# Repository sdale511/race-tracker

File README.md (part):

# Race Tracker — Boat Agent + Base Station

Reports GPS position from a boat (Pi Zero 2 W + simpleRTK2B LR) to a shore/
committee base station over a long-range telemetry radio (>2 mi), with
logging to microSD as a durable backup.

## Architecture

```
[simpleRTK2B LR]--UART-->[Pi Zero 2 W]--UART-->[Telemetry radio]==RF==>[Telemetry radio]--UART-->[Base station]--> race software
                              |
                              v
                    microSD (CSV, same fixes sent over radio)
```

For the complete rover → base → RegattaUp data flow - wire formats, Redis
keys, webhook payloads, RegattaUp's own entity fields - see
[`docs/telemetry-pipeline.html`](docs/telemetry-pipeline.html) (open in a
browser).

| Component | Notes |
|---|---|
| GPS | ZED-F9P, `UBX-NAV-PVT` binary messages (position, speed, heading, fix type, RTK carrier solution, satellite count) - no NMEA needed |
| Radio | Digi XBee 900 MHz in transparent serial mode (any transparent-serial radio works, e.g. RFD900x/SiK). A compact 26-byte binary frame (`src/protocol.js`) minimizes airtime - batched 8 at a time by default (delta-coded, 83 bytes), see `TX_BATCH_SIZE` below |
| SD log | Logged exactly when a fix clears the `TX_DISTANCE_M`/`TX_INTERVAL_S` gate - same gate as the radio send, so the SD record mirrors what actually transmitted rather than a separate full-rate trace |

**How the gate measures.** A fix clears the gate when the boat has moved `TX_DISTANCE_M` (default 1 m) from the last fix that *cleared* it, or `TX_INTERVAL_S` (default 60 s) has passed since then - the last fix that cleared the gate, not the last one actually sent (`distanceGate.js`). In slot mode a fix waits up to a cycle for its slot; measured from the last fix *sent*, the gate stayed open for that whole wait, so a boat creeping at 1.3 kn sent clusters of eight fixes a millimetre apart, then nothing for two seconds, and a heartbeat that fell due sent eight copies of one position. Now consecutive fixes are at least `TX_DISTANCE_M` apart and a heartbeat adds one fix. A boat faster than about 19 kn at 10 Hz moves more than a metre per fix, so it still sends every fix. A send that fails (radio not connected yet) hands the reference back to the last fix that really went out, so the boat keeps retrying.

## Wiring notes

Default config uses the Pi's own dedicated hardware UART (`/dev/ttyAMA0`,
GPIO 14/15 - avoid the mini-UART, its clock is tied to the core clock and
can glitch), leaving the one USB/OTG port free for the telemetry radio
alone.

```
sudo raspi-config   # Interface Options -> Serial Port
                     # "login shell over serial" = No
                     # "serial port hardware enabled" = Yes
```

- Prefer the simpleRTK2B's own USB port (`/dev/ttyACM0`) instead? Set
  `GPS_PORT=/dev/ttyACM0` (and matching `GPS_BAUD`) - simpler wiring, but
  needs a USB hub since the radio then needs its own USB-to-serial adapter.
- Any Pi with onboard Bluetooth (Zero 2 W, 3A+/3B+, 4, ...) puts GPIO14/15
  on the glitch-prone mini-UART (`ttyS0`) by default, since Bluetooth
  occupies the real UART. Fix:
  ```
  # /boot/firmware/config.txt (Bookworm+) or /boot/config.txt (older)
  dtoverlay=disable-bt
  ```
  then disable `hciuart`/`bluetooth` services and reboot.
- Which physical UART (UART1 vs UART2) your wiring reaches depends on the
  board - ArduSimple's simpleRTK2B routes UART2 to the XBee socket (used
  for RTCM correction radios, unrelated to this app), so a general
  breakout pin is more likely UART1 - verify, don't assume (see below).

### Radio sleep wiring (XBee SLEEP_RQ)

Optional - only needed for rover radio sleep mode (see "Radio sleep mode"
below). One extra wire from a Pi GPIO to the XBee's SLEEP_RQ pin, next to
the radio's UART wiring above:

| From | To | Notes |
|---|---|---|
| Pi **GPIO17** (header pin 11, 3.3 V) | XBee **pin 9** (SLEEP_RQ / DTR) | High = radio asleep, low = awake |
| Pi GND (header pin 9, right next to pin 11) | XBee GND | Shared ground, usually already there via the UART wiring |
| 10 kohm resistor | XBee pin 9 to GND | Pull-down, so the radio stays awake while the Pi is off or still booting |

- **Why GPIO17:** GPIO9-27 are pulled *down* at boot, whereas GPIO0-8 are
  pulled *up* and would put the radio to sleep during every Pi boot. GPIO17
  also isn't claimed by anything this app uses or by a default overlay (UART
  GPIO14/15, I2C GPIO2/3, SPI GPIO7-11, 1-wire GPIO4, PWM/PCM GPIO12/13/18/19),
  and sits on header pin 11 with GND on pin 9 beside it, so one short
  cable can carry the UART (pins 8/10) and this wire. Any other free GPIO
  from 9-27 works; set `RADIO_SLEEP_GPIO` to its BCM number.
- **XBee setting:** the radio must be in pin-sleep mode - `ATSM1`, then `ATWR`
  (for example from XCTU). `xbee_configure_at.py` does not set this. Do it only
  once the wire and pull-down are in place, because in `SM=1` a pin driven
  high puts the radio to sleep and it cannot be reached over the UART until
  the pin goes low again.
- **If the radio is on a USB-serial bridge** whose DTR line is also wired to
  XBee pin 9 (needed only for serial firmware updates), use a jumper or
  solder bridge so just one of the two drives the pin - never both.
- Optional: XBee ON_SLEEP (pin 13) to a spare Pi GPIO input, or an LED, to
  see the radio's actual sleep state. The app doesn't read it.
- `RADIO_SLEEP_GPIO=17` tells the rover app which pin to drive. Unset (the
  default), a real rover ignores sleep commands. It uses Raspberry Pi OS's
  `pinctrl` command to drive the pin.

### GPS backup battery (V_BCKP)

Not a wire - a factory option on the ArduSimple board. It keeps the GPS's
satellite data alive so the rover restarts hot instead of cold. Whether your board
needs it is something to check, not assume: see "Checking and fitting the GPS
backup battery" under "Radio sleep mode".

## GPS configuration (one-time, from a computer)

The rovers never configure the GPS module or the radio - the Pi only reads fixes. Set the ZED-F9P up from a computer
over the board's own USB port, with `ubx_config_set.py` (or u-center):

```
pip install pyserial
python3 ubx_config_set.py --port <the board's USB port> --role rover-pi --dry-run   # shows what it would change
python3 ubx_config_set.py --port <the board's USB port> --role rover-pi
```

`rover-pi` is the Pi rover's profile and keeps UART2 on, so the XBee in the board's socket feeds the receiver directly.
Plain `rover` is the ESP32 rover's (`firmware/esp32-rover`), which switches UART2 **off** - don't use it on a Pi boat,
whose corrections would then stop reaching the receiver.

The rover profile turns `UBX-NAV-PVT` on (without it this app sees nothing), sets 10 Hz, disables TMODE3, turns
`UBX-RXM-RTCM` on, sets UART2's baud to match the XBee in the board's socket, and sets UART1 (the port the Pi reads) to
115200 with UBX output on. It writes to RAM, BBR and flash, so it
survives a power cycle, and reads every value back. Each UART is configured independently - the UART the Pi's wires reach
may still be at factory defaults (NMEA on, UBX off) even after another port was configured. The profile sets
`UBX-NAV-PVT` on UART1; if the Pi's wires reach UART2, check with the verification step below. The XBee is configured
separately with `xbee_configure_at.py`. Don't install `gpsd` on a rover - it grabs the serial port.

To see what a port is outputting before you configure anything, try the common bauds (9600, 19200, 38400, 57600,
115200) until you see clean `$GNGGA`/`$GNRMC`/... text:

```
stty -F /dev/ttyAMA0 <baud> raw -echo
cat /dev/ttyAMA0        # Ctrl-C to stop
```

`sudo ./setup-pi.sh uart` on the Pi only frees the UART (serial console off, Bluetooth off, `dialout` group); it does not touch
the GPS module.

### Checking the antenna gets both bands

Dual-band RTK needs L2 as well as L1, and an antenna that only passes L1 still gives a normal-looking fix. While a rover's
dashboard is open, its **GPS signals** card asks the receiver for `UBX-NAV-SIG` every few seconds and shows satellites and
average C/N0 per band and per constellation, with a verdict: L1 + L2, L2 weak, L1 only, or too few satellites to judge.
"L2" includes Galileo E5b and BeiDou B2I, and a gap of a few dB under L1 is normal. The weak thresholds in
`src/gnssSignals.js` are rules of thumb. The card also shows whether the telemetry radio hurts reception: compare it with
the radio transmitting and silent. It needs the Pi TX line wired to the receiver RX, and it doesn't ask while the GPS
sleeps, because any byte would wake it. Nothing on the receiver is reconfigured.

### Verifying the connection

```
stty -F /dev/ttyAMA0 115200 raw -echo
cat /dev/ttyAMA0        # expect quiet gaps + a short binary burst ~1/sec
```
Then confirm this app itself decodes it (the check that actually matters):
```
GPS_PORT=/dev/ttyAMA0 GPS_BAUD=115200 npm run boat
```
Watch for `[gps]` lines with real `fixType`/`numSV` (see `GPS_LOG`; `npm run print-config` lists every
setting). Silence means `UBX-NAV-PVT` went to the wrong UART number
- undo (`CFG-MSGOUT-UBX_NAV_PVT_UARTx,0,7`) and try the other.

The simpleRTK2B LR's onboard radio (in the board's XBee socket) is a
**separate concern** - it carries RTCM3 correction data between RTK base
and this rover, not position telemetry. "LR" is ArduSimple's own kit name
("Long Range," about 10 km), not a Digi product name - confirmed off the
module's label, the chip is a **Digi XBee SX** (Model XBSX, FCC ID
`MCQ-XBSX`); the step-up "XLR" kit uses a Digi XBee PRO SX for longer
range.

### RTK base GPS: enabling RTCM3 output (one-time)

`TMODE3` (fixed/survey-in position, set from this app's `npm run
rtk`/`basertk` dashboard) and RTCM3 *output* are separate config groups -
setting a fixed position doesn't turn sending RTCM on. Some kits ship with
only `1005` enabled and no observation messages, which looks like "locked
and working" on the dashboard while the rover receives nothing usable.

Check/enable on the base's correction-radio UART (`UART2` on the
simpleRTK2B LR - its onboard XBee SX is wired internally to UART2, not
something you'd jumper yourself):

| Message | Content |
|---|---|
| `1005` | Station coordinates (depends on the fixed position) |
| `1074`/`1084`/`1094`/`1124` | MSM4 observations: GPS/GLONASS/Galileo/BeiDou |
| `1230` | GLONASS code-phase biases (needed alongside `1084`) |

Send **one** observation set, MSM4, not MSM4 and MSM7 together. MSM7 carries
the same observations at higher resolution and about 1.5x the bytes; sending
both is duplicate traffic (an audit found a board doing exactly that - the
factory MSM4 plus an MSM7 set added on top - roughly 2.5x the bytes the rover
needs). MSM4 is also the better fit for this fleet's radios: a whole epoch is
about 400 bytes, and individual messages stay near the 100-byte radio packet
limit (MSM7 messages go well past it and get split in two over the air, and
losing either half loses the message).

```
ubxtool -f <base GPS port> -s <baud> -P 27.11 -z CFG-MSGOUT-RTCM_3X_TYPE1005_UART2,1,7
ubxtool -f <base GPS port> -s <baud> -P 27.11 -z CFG-MSGOUT-RTCM_3X_TYPE1074_UART2,1,7
ubxtool -f <base GPS port> -s <baud> -P 27.11 -z CFG-MSGOUT-RTCM_3X_TYPE1084_UART2,1,7
ubxtool -f <base GPS port> -s <baud> -P 27.11 -z CFG-MSGOUT-RTCM_3X_TYPE1094_UART2,1,7
ubxtool -f <base GPS port> -s <baud> -P 27.11 -z CFG-MSGOUT-RTCM_3X_TYPE1124_UART2,1,7
ubxtool -f <base GPS port> -s <baud> -P 27.11 -z CFG-MSGOUT-RTCM_3X_TYPE1230_UART2,1,7
```
`ubx_config_set.py --role base` (below) does all of this on both UART1 and
UART2 and also switches the MSM7 messages off, which these commands alone don't.
Only enable constellations you're actually tracking. `,7` saves to flash
immediately (bare `,1` is RAM-only, for testing before committing).

For visibility into corrections arriving rover-side, enable `UBX-RXM-RTCM`
on the rover's own GPS UART and set `RTCM_LOG=1` (off by default; `GPS_LOG_RTCM` is the old name and still works):
```
ubxtool -f /dev/ttyAMA0 -s <baud> -P 27.11 -z CFG-MSGOUT-UBX_RXM_RTCM_UART1,1,7
```
Watch `[rtcm]` lines (`type=1074 station=0 used=used`) - `used=not used` on
its own is normal (unused constellations), `CRC-FAILED` means a correction
arrived corrupted. Message counts/CRC failures are always tracked
internally (`GET /api/stats`) regardless of this flag.

### RTK base GPS: enabling the survey-in status card (optional)

If the "Base GPS survey-in" card shows "no base GPS, or not polled yet"
even with `GPS_PORT` set and TMODE3 configured for survey-in,
`UBX-NAV-SVIN` likely isn't enabled as an output:
```
ubxtool -f /dev/ttyAMA0 -s 115200 -P 27.11 -z CFG-MSGOUT-UBX_NAV_SVIN_UART1,1,7
```
Configuring TMODE3 itself for survey-in (vs. just reading it) is a
separate one-time step, typically done via u-center at setup - see
u-blox's ZED-F9P integration manual for survey-in parameters.

### Checking everything at once (ubx_config_report.py)

`ubx_config_report.py` polls every setting the sections above depend on - fix rate, UART baud,
`UBX-NAV-PVT`/NMEA/`UBX-NAV-SVIN`/`UBX-RXM-RTCM` output, TMODE3 mode, RTCM3 output types - in one pass, instead of
polling each by hand or assuming a board's still configured the way it was last time. It talks the UBX binary protocol
directly over `pyserial` (no `gpsd`/`ubxtool` needed - same reasoning as `xbee_configure_at.py`'s own "why not a
library" comment) and is read-only:
```
pip install pyserial
python3 ubx_config_report.py --port /dev/ttyAMA0 --baud 115200
```
A board acting as a rover should show the RTK-base rows (TMODE3, RTCM3 output) at 0/off; a board acting as the RTK base
should show its own rows enabled and `CFG-TMODE-MODE` non-zero. `--comms` instead measures the bytes sent and received
on each port over a few seconds (`--comms-seconds`, default 5). Every key ID it polls is cross-checked against two
independent open-source references (SparkFun's u-blox GNSS library and pyubx2), not typed from memory - see its own
module comment.

`ubx_config_set.py` applies the fix, same no-`ubxtool`-needed approach:
```
python3 ubx_config_set.py --port /dev/ttyAMA0 --baud 115200 --role base
python3 ubx_config_set.py --port /dev/ttyAMA0 --baud 115200 --role rover-pi
```
`--role base` makes the base's RTCM output clean: `1005`, the MSM4 observations
(`1074`/`1084`/`1094`/`1124` - GPS/GLONASS/Galileo/BeiDou) and `1230` on, the
MSM7 messages (`1077`/`1087`/`1097`/`1127`) explicitly off, RTCM3 allowed as an
output protocol, and `UBX-NAV-SVIN` on - on the ports named by `--rtcm-ports`
(default `uart2,usb`: UART2 is the onboard correction radio, USB the host
connection), with every other port's RTCM switched off so nothing is sent where
nothing reads it. Add `uart1` only if something reads the board on the Pi header
UART. `--constellations` (default all four) leaves constellations out to save
bytes - a left-out one has its MSM4 message off, and `1230` goes with GLONASS.
`--rtcm-interval N` (default 2) sends every enabled message every N seconds instead of every
second (it sets the messages' output rate in measurement epochs, and the base profile also sets the receiver's
measurement rate to 1 Hz so an epoch is a second - at the rover profile's 10 Hz, "2 epochs" would be 0.2 s, about eight
times the intended correction airtime, which is what happens if the rover profile is ever applied to a base receiver):
`--rtcm-interval 2` halves the correction airtime, at the cost of rovers working from corrections up
to 2 s old and a lost message costing 2 s. Check that RTK still holds at speed before relying on it.
`--station-interval N` (default 10) sends the 1005 station-position message every N seconds instead of with every burst
(never more often than `--rtcm-interval`). The base's position is fixed, so a rover only needs to hear it now and then; it
is what a rover needs before it can start an RTK fix, so a boat that powers up waits up to N seconds for its first one.
Sending it less often also removes a small message that would otherwise arrive a second away from the observations.

Run it with `--dry-run` first to see exactly what would change, and
`ubx_config_report.py` afterwards to confirm; it writes RAM+BBR+flash, so it
survives a power cycle.
```
python3 ubx_config_set.py --port /dev/cu.usbmodem101 --role base --dry-run
python3 ubx_config_set.py --port /dev/cu.usbmodem101 --role base --constellations gps,galileo,beidou
```

The RTCM message rates are written together, in one command (off, then on), whenever any of them changes: each message's output
counter starts when its rate is written, so rates written one by one can end up on different seconds. `--realign-rtcm` does the
same off-and-on for a receiver whose rates already read correctly. To see what the base is really sending, with every message's
arrival time and the gaps between them (stop the base first so the radio port is free):
```
python3 rtcm_listen.py --port /dev/cu.usbserial-0001 --seconds 20 --timeline
```

The base role also prints the receiver's current TMODE3 mode as its first line
(`TMODE3 mode = 1 (survey-in)`, `2 (fixed position)` or `0 (disabled)`). A receiver is only a base while TMODE3 is
survey-in or fixed; at 0 it sends no usable corrections and the admin dashboard's survey-in card says "disabled".
That happens when the rover profile, which sets TMODE3 to 0, is applied to the same receiver. So **if it reads 0 the
base role turns survey-in on** (the receiver averages its own position for at least `--svin-min-dur` seconds, default
300, until it is within `--svin-acc-limit-m` metres, default 2.0, then starts sending corrections; the dashboard's
survey-in card shows the progress). A fixed position or a survey already running is left alone. `--survey-in` forces
survey-in even over a fixed position, replacing it:
```
python3 ubx_config_set.py --port /dev/cu.usbmodem101 --role base --dry-run               # shows what it would do
python3 ubx_config_set.py --port /dev/cu.usbmodem101 --role base --survey-in             # replace a fixed position
```
Survey-in gives a new averaged position, which can differ by a metre or two from an earlier surveyed or fixed one - if
the course marks were planted against the old reference, restore the old fixed coordinates or plant them again.

This replaces an earlier profile that added MSM7 on top of the board's factory
MSM4 (a live audit then found both sets going out the radio). The original gap
it was written for - `1005` station coordinates on and no observation message at
all, so a rover would never get a usable correction - is still covered. All four
constellations are on by default, not gated behind opt-in flags - this fleet
operates in the US, where all four have real satellites in view (including
BeiDou-3's global coverage, not just the old Asia-Pacific-only BeiDou-2), and more
satellites means better RTK fix reliability under real-world sky obstruction;
pass `--constellations` (below) if you want fewer.
`--role rover-pi` (and the ESP32's `--role rover`) enables `UBX-NAV-PVT`
(required, or this app sees nothing from it), disables TMODE3 (a rover
isn't a stationary reference station), enables `UBX-RXM-RTCM` (for
`RTCM_LOG` visibility), and sets the fix rate to 10Hz (`CFG-RATE-MEAS`)
- not the ZED-F9P's 20Hz spec ceiling, to leave headroom. (An earlier version of
this note cited u-blox's "link latency under nav-period minus 50ms" rule; the
integration manual gives that rule for *moving-base* RTK only, not for a
stationary base like this one, so it isn't a reason for 10Hz here. For a
stationary base the manual's documented limit is that the rover stops using
corrections older than 60 s - `CFG-NAVSPG-CONSTR_DGNSSTO`.)
It also accepts RTCM3 as an input on UART2 (the correction radio's port),
makes sure GPS/GLONASS/Galileo/BeiDou tracking are all on (the rover can only
use corrections for constellations it tracks) and sets the differential mode to
3 = RTK fixed (2 would stop at float).

**Both roles** set UART2's baud (`--uart2-baud`, default 115200) - UART2 is the
port the onboard correction radio is wired to, so it **must equal that radio's
own baud** (the base's reads 115200). If your correction radios aren't at
115200, pass their baud instead of accepting the default.

**Both roles** also set UART1, the port the Pi reads, to `--uart1-baud` (default
115200 - must equal the app's `GPS_BAUD`) with UBX output on. The boards come
from ArduSimple at 115200, but a receiver that loses its configuration falls back
to u-blox's factory 38400, and the Pi then reads only garbage (`e0 1c fc 70`...
bytes on `/dev/ttyAMA0`). Re-running the profile over USB fixes it; through the
Pi's own UART, connect at the old baud (`--baud 38400`) - UART1's baud is written
last and the script reconnects at the new one to check it. If nothing answers at
`--baud` at all, the script says so and stops.

Every write goes to
RAM+BBR+Flash (survives a power cycle) and is read back afterward to
confirm it actually stuck - a silently-failed write is worse than a loud
one. `--dry-run` shows what would change without writing anything.

## Radio configuration

Pair every radio (boat + base) on the same netid/frequency/baud, in
transparent-serial mode.

| | Factory default | This app's default |
|---|---|---|
| XBee baud | 9600 | **115200** |
| RFD900x/SiK baud | 57600 | **115200** |

At fleet sizes beyond a couple boats, the base↔radio serial link (every
boat's frames funnel through one port) becomes the bottleneck well below
the radio's actual RF capacity - hence 115200. Reconfigure **every**
radio's serial baud via XCTU (XBee) or RFD Modem Tools/Mission Planner
(RFD900x) before running with this default; a mismatch just means the
port opens but nothing decodes. Also confirm all radios share the same
Network ID (XBee `ID`).

**Don't raise this past 115200 without re-testing.** It's tempting to - a
100-boat `radio-congestion` run at 115200 measured the SERIAL link
saturating at about 11.2 KB/s, almost exactly 115200's own 8N1 ceiling (115200 ÷
10 bits/byte = 11,520 B/s), apparently well under an XBee-PRO 900HP 200K's
nominal RF capacity. Bumping to 230400 does relieve that serial ceiling
(the same test then pushed 15.4 KB/s, using only about 67% of 230400's own
about 23 KB/s ceiling) but sync errors jumped from 0.2% to 10.4% - real
RF-level bit corruption (see `radioLink.js`'s own `sync-error` event), not
local serial buffering, since bandwidth used stayed well under the new
ceiling. This fleet's actual radios' real sustainable RF throughput tops
out around 11-12 KB/s regardless of serial baud - 115200 was accidentally
already throttling right at that ceiling, not artificially limiting it.
`TX_BATCH_SIZE` (reduces actual RF bytes-per-fix, not just how fast the
serial link can be fed - see "Batching multiple fixes per send" below) is
already at its practical ceiling by default (4, `MAX_BATCH_COUNT`) - there's
no more headroom left there to reach for if you need still more real fix
throughput. Re-run the same `radio-congestion` test checking sync-error
rate, not just bandwidth headroom, before trusting any higher baud.

Running only 1-2 boats? Leave everything at factory defaults and set
`RADIO_BAUD` to match. Higher baud = faster delivery but shorter
range/reliability at a given power - tune on the water. **Antenna height
matters a lot for going over water at >2mi.**

### Configuring XBee radios (xbee_configure_at.py)

For XBee-PRO S3B (900HP/XSC) radios, `xbee_configure_at.py` (repo root)
automates the above instead of using XCTU by hand: DigiMesh delivery mode,
routing/relaying disabled on every node (single-hop fleet only), matching
Network ID/DH-DL/HP/MT/BD. Every command/value comes from Digi's XBee-PRO
900HP/XSC S3/S3B User Guide - not `MM`/`CH`/`CD`, which don't exist on
this module (confirmed live: both `ERROR`). No base-vs-rover split - every
radio gets identical config. Speaks plain AT Command Mode over `pyserial`
("+++", "ATxx<value>", "ATWR") - never leaves transparent mode.

```
pip install pyserial

python3 xbee_configure_at.py --port /dev/ttyUSB0             # every radio
python3 xbee_configure_at.py --port /dev/ttyUSB0 --dry-run    # read only
python3 xbee_configure_at.py --port /dev/ttyUSB0 --role rtcm  # an XBee-PRO 900HP as the RTK correction radio
```

| Flag | Default | Notes |
|---|---|---|
| `--connect-baud` | 115200 | The radio's CURRENT speed - pass its actual current baud if already reconfigured, or `9600` for a genuinely factory-fresh radio |
| `--target-baud` | 115200 | Applied last (changes how the script itself talks to the radio), matches `RADIO_BAUD` |
| `--mode` | `p2mp` | `p2mp` / `digimesh` / `digimesh-routing` |
| `--role` | `telemetry` | What the radio is for. `telemetry`: network ID `0x7FFF`, `HP` 0, `MT` 0 (the position link). `rtcm`: network ID `0x1985`, `HP` 1, `MT` 1 (each broadcast sent twice), no flow control - the RTK correction link on its **own network**, so a yacht's two XBee-PRO 900HP radios never hear each other's data. Set **both ends** of each link the same |
| `--network-id` / `--preamble-id` / `--mt` | from `--role` | Override a single value of the preset: `ID` (0 - 0x7FFF), `HP` (0 - 7), `MT` (0 - 5) |
| `--flow-control` | `cts` | `none` (D7=0, D6=0) / `cts` (D7=1, D6=0 - Digi's own factory default) / `rtscts` (D7=1, D6=1). CTS is an output the radio raises when its serial buffer is nearly full - harmless if the host ignores it. **RTS makes the radio stop sending to the app while RTS is held high**, so use `rtscts` only with an adapter whose RTS line is wired and driven, or the radio goes silent to the app. The app itself opens the port without hardware flow control today, so these settings only take effect once it (or the adapter's driver) honours them |

**Encryption (`EE`) is switched off** by the script (and `--dry-run` shows it as the `EE (Encryption)` row). With AES on, every RF packet loses 9 bytes of its 100-byte payload, so the marks frame (91 bytes) would still fit but the slot table (up to 97) and power (up to 95) frames would be split across two packets and lost if either half is. `EE` has to be the same on every radio in the network, so run the script on all of them (or check each with `--dry-run`).

**The node identifier (`NI`) is the one setting a boat writes itself.** In boat mode (not mark mode, and not
`SIMULATE=1`) the boat sets its telemetry XBee's `NI` to its `BOAT_ID` when the radio port first opens, so a radio taken
out of a boat, or listed by XCTU's network discovery, says which boat it belongs to. It enters AT command mode the same
way this script does (`+++` with a 1.1 s guard time), reads `NI`, and writes and saves it (`ATNI`, `ATWR`) only when it
is different, so a normal boot writes nothing to the radio's flash. That adds about 2 s before the radio is ready,
and nothing is transmitted in the meantime. The start log shows `xbee node identifier (NI): setting to "<id>"` with the
other startup lines, then `already "<id>"`, `set to "<id>" (was "...")`, or why it could not (for example a radio in API
mode, which never answers `+++`); the boat carries on either way.

The stock ArduSimple LR radio's settings, side by side with each preset above, are
recorded in [`docs/xbee-radio-settings.md`](docs/xbee-radio-settings.md).

**Not for the stock ArduSimple long-range radios.** Those are XBee SX modules
paired on their own network ID (`0x1985`); running this script for real on one
would change its settings (a dry run is safe and just reads them). `--role rtcm` is
for replacing *both* ends of the correction link with XBee-PRO 900HPs; try it on the
bench first (ZED to radio to radio to ZED, with `RTCM_LOG=1` on the rover) before
relying on it. `CM` (the channel mask) is still not set by this script, so two
900HP networks on one yacht still hop across the same frequencies.

Config values (network ID, DH/DL, etc.) live in the `CONFIG` dict at the
top of the script, not as flags, except those the flags above override. Channel selection (`CM`) isn't touched at
all - set by hand first if avoiding specific frequencies. Only one process
can hold a serial port - stop any running `npm run base`/`boat`/`radio-test`
or XCTU on that port first.

**Mode history**: DigiMesh (`TO=0xC0`) is confirmed-working and was the
long-time default. Point-to-Multipoint (`TO=0x40`, lower overhead, no
network header) failed traffic between two persistently-verified P2MP
radios on this hardware - a real incompatibility, not config/persistence.
As of this pass **P2MP is the new default** based on further review (one
open lead: DigiMesh's own broadcasts already reuse Directed-Broadcast wire
framing, not unique DigiMesh framing, since this app's traffic is 100%
broadcast - so the earlier "working" DigiMesh test never actually
exercised mesh-routing behavior). Fall back with `--mode digimesh` if P2MP
doesn't work on your hardware. A real (non-dry-run) run soft-resets (`FR`)
and reconnects to re-verify every parameter survives a reboot, not just
reads back correctly mid-session.

### Bench-testing the radios

```
RADIO_TEST_MODE=send   RADIO_PORT=/dev/cu.usbserial-A npm run radio-test
RADIO_TEST_MODE=listen RADIO_PORT=/dev/cu.usbserial-B npm run radio-test
```

`src/radioTest.js` exercises the real radio link directly (no GPS, Redis,
or simulation) using the exact same `RadioLink`/`protocol.js` code
production uses. One instance per radio (`ls /dev/cu.*` before/after
plugging in to find device paths on macOS). `RADIO_BAUD` and Network ID
(`ATID`) must match on both.

Sender transmits one frame every `RADIO_TEST_INTERVAL_MS` (default 500ms)
with a sequence number in the timestamp field. Listener logs received
frames and prints a running summary every 10s (received count, estimated
missed, loss %). Start close together to confirm connectivity, then
separate to find where the link degrades.

**Measuring radio latency and the slot guard (`radio-latency`).** A time-slot schedule needs a
*guard time* - how much a frame's arrival can vary - and that should be measured, not guessed.
Two radios on one machine, one sending and one listening, give one-way latency from "the app wrote
the frame" to "the other radio's app decoded it", with the send and receive times from the same clock:

```
LATENCY_TX_PORT=/dev/cu.usbserial-5 LATENCY_RX_PORT=/dev/cu.usbserial-0001 npm run radio-latency
```

1. Power the RTK base and let it send corrections (so there are RTCM bursts to measure against).
   With the base off the test still gives latency, just without the near-burst comparison.
2. Put two radios on the machine, both on the **same network** as the base (same `ID` and `HP`,
   115200 baud). `ls /dev/cu.*` before and after plugging each in to find their ports.
3. Stop anything else holding those ports (`cat`, miniterm, `npm run boat`, `rtcm_listen.py`).
4. Run the command above (about 80 seconds for 300 frames). Leave the radios alone while it runs.
5. Read the report: one-way latency percentiles (min, p50, p90, p99, max) and jitter (p99 - p50);
   latency and loss for frames sent *near* an RTCM burst versus *clear* of it; whether bursts that
   had a test frame near them came through incomplete more often than the others (that is what a
   telemetry transmission costs the corrections); and a suggested guard.
6. Repeat for a bigger frame and a longer run: `LATENCY_BATCH=8 LATENCY_FRAMES=600 ...` (an 83-byte delta frame of 8 fixes, the biggest a boat sends; `LATENCY_DELTA=0 LATENCY_BATCH=4` for the older 84-byte
   batch frame).
7. Swap which radio sends and which listens (the two ports) and run again, to see that the numbers
   don't depend on the radio.

Settings: `LATENCY_FRAMES` (300), `LATENCY_GAP_MS` (250, plus a random 0-40 ms so sends cover every
phase of the second), `LATENCY_BATCH` (1 = a 26-byte frame, 2-8 = a delta-coded frame of that many fixes - 8 is 83 bytes; `LATENCY_DELTA=0` sends the older batch frame instead, 2-4 fixes up to 84 bytes). The test fixes move, so every field of a delta frame is exercised, and the report counts frames that arrived with a good checksum but decoded to different values than were sent (radio corruption the additive checksum missed - it should be 0),
`LATENCY_FOCUS=1` (send only in a sweep from 80 ms before to 160 ms after each predicted correction burst, one frame per burst, to find exactly where sending hurts; needs the base running; 150 frames, about 150 s), `RADIO_BAUD` (115200). The guard it suggests is a starting point: one machine, two adapters. It does
not include a Raspberry Pi's own delays, so repeat it on a Pi before setting slot timing.

**Testing the transmit scheduler itself (`LATENCY_SCHEDULE`).** The same two-radio setup can run
the real `TxScheduler` instead of sending at random times, so you can see what the gate and the
slots do to the corrections. The sender radio listens for the base's bursts to learn the timing
(it waits for 3 bursts before sending), then each virtual boat sends through its own scheduler.

```
# A: no gate (baseline) - existing random-phase run, same load
LATENCY_BATCH=2 LATENCY_FRAMES=300 LATENCY_TX_PORT=<sender> LATENCY_RX_PORT=<listener> npm run radio-latency
# B: gate only - telemetry held out of the correction window
LATENCY_SCHEDULE=gate  LATENCY_BATCH=2 LATENCY_FRAMES=300 LATENCY_TX_PORT=<sender> LATENCY_RX_PORT=<listener> npm run radio-latency
# C: gate + slots - two virtual boats in slots 3 and 7, 45 ms wide (the default; the measurements below used 35). Add LATENCY_BATCH=8 LATENCY_GAP_MS=2000 for one 83-byte frame per 2 s cycle (a boat at 8 Hz sends two per cycle)
LATENCY_SCHEDULE=slots LATENCY_SLOTS=3,7 LATENCY_SLOT_MS=45 LATENCY_TX_PORT=<sender> LATENCY_RX_PORT=<listener> npm run radio-latency
```

The report shows, per boat, when each frame was actually written relative to the burst start
(slot mode: it should sit at the slot's opening, `30 + slot x slot width` ms), how long frames were
held, frames written inside the conflict window (should be 0), arrivals from different boats within
15 ms of each other (should be 0; the closest gap is printed too - neighbouring slots give about 21 ms or more), and bursts that came through incomplete with and without a
frame near them. Compare the incomplete-burst rate in A against B and C. `LATENCY_BOATS` sets the
number of virtual boats (default 1 for `gate`, one per `LATENCY_SLOTS` entry for `slots`).

**Looking at the raw bytes on a radio's port (macOS).** Don't use `stty -f <port> 115200`
followed by `cat <port> | xxd`: macOS resets the port to its default 9600 baud when
`cat` reopens it, so a 115200 radio's output reads as noise. Use a tool that sets the
baud itself when it opens the port - `python3 -m serial.tools.miniterm <port> 115200 --raw`,
or `rtcm_listen.py`:

```
python3 rtcm_listen.py --port /dev/cu.usbserial-0001 --seconds 20
```

`rtcm_listen.py` decodes the stream rather than dumping hex: checksum-valid RTCM3
messages (with type and size), UBX frames and NMEA sentences, how many bytes it
couldn't recognise, and how wide each second's burst is. "No valid frames" there
means the bytes really are corrupted, unlike a wrong-baud `cat`.

### Congestion-testing the radio

`npm run fleet`'s `SIMULATE=1` link is UDP with no airtime limit, so it
can't show real congestion; running real `FLEET_SIZE` boats needs one real
radio *per boat*. `src/radioCongestionTest.js` instead runs one process,
one real radio, transmitting the *combined* frame traffic a whole
simulated fleet at speed would put on the air - same
`protocol.js`/`RadioLink` frames, same per-boat `TX_DISTANCE_M` cadence,
computed directly rather than from a live GPS track.

```
npm run base                                                   # real base, real radio - NOT SIMULATE=1
BOAT_COUNT=30 RADIO_PORT=/dev/cu.usbserial-A npm run radio-congestion
```

The base treats this synthetic traffic exactly like a real fleet's - real
(non-zero) lat/lon, real-format boat ids - so with a real regatta selected
it gets written into that regatta's own Redis data (and, if RegattaUp
reporting is live, could fire real lap/on-grid webhook posts too). Run the
base with `NO_REGATTA=1 npm run base` for a pure bench test instead: it
skips regatta auto-selection entirely for that run (no terminal prompt, no
closest-active-date auto-pick), so every received frame - real or
synthetic - is ignored and nothing is written anywhere. The admin
dashboard's own regatta dropdown still works normally if you want to
override it mid-run.

Watch the base's fleet dashboard (last-seen/frame counts) and its
`[radio] link quality` log line (sync errors) as `BOAT_COUNT` climbs.
`CONGESTION_SPEED_KN` (default 26.1, ≈ 30mph - this fleet's own reference
planning speed, land yachts rather than displacement sailboats; still in
knots like every other speed value in this app, so a bare `30` here means
30 *knots* instead) sets the assumed speed driving send rate. This tests
airtime/throughput load on the base's real receive
pipeline - it is **not** a test of real multi-transmitter RF collisions
(every frame still leaves one real antenna); that needs one real radio per
virtual boat.

**For real collisions**, run several of these at once, each on its own
physical radio, `BOAT_ID_OFFSET`-staggered so their boat ids don't overlap
(purely cosmetic for telling frames apart on the dashboard - the actual RF
collision behavior only depends on the radios being physically separate
transmitters, not on the ids). Split a target fleet size across them to
get realistic aggregate load *and* genuine multi-transmitter contention at
once, rather than choosing between the two:

```
BOAT_COUNT=7 BOAT_ID_OFFSET=0  RADIO_PORT=<radio1> npm run radio-congestion
BOAT_COUNT=7 BOAT_ID_OFFSET=7  RADIO_PORT=<radio2> npm run radio-congestion
BOAT_COUNT=7 BOAT_ID_OFFSET=14 RADIO_PORT=<radio3> npm run radio-congestion
BOAT_COUNT=7 BOAT_ID_OFFSET=21 RADIO_PORT=<radio4> npm run radio-congestion
```

Physically separate the transmitting radios rather than clustering them -
radios that can all hear each other collide differently (often more
politely) than ones spread across a real course, where some pairs are
hidden nodes to each other but both still reach the base. That hidden-node
case is usually where the ugliest real collision behavior actually shows
up, and clustering hides it entirely.

### Marking the base's own log from a rover

A real field test - walking/driving a rover to a new distance from the
base, checking an antenna, anything worth timestamping - needs a way to
say "right now" without cross-referencing two separate logs by wall-clock
time afterward. Every rover's own dashboard (`roverAdminServer.js`, any
mode - plain boat or mark) has a **Mark base log** card: type a
short note (20 characters, truncated beyond that) and tap **Mark**. It
sends over the same telemetry radio a position fix already goes out on
(`protocol.js`'s `encodeMarkLog`/`0x88`) - no GPS fix or WiFi needed, works
even before this device has ever gotten a position.

The base logs it unconditionally to its own console
(`=== MARK from boat=... : "<note>" ===`), and - when `LOG_RATE_STATS=1` is
also set (see "Congestion-testing the radio" above) - appends it as its
own row in that same `base_station_rate_stats_<date>.csv`, numeric fields
blank, note filled in, landing inline with the fix-rate/error-rate time
series at the exact moment it was sent.

`radio-congestion` runs its own copy of this same dashboard too - same
port as any other rover's own admin dashboard (`ADMIN_PORT`, default 8092;
8093 under `SIMULATE=1`, same as `boatAgent.js`) - purely to reach this
card from a browser during a bench test. Every other card on
it (course marks, GPS fix, uploads, scheduled shutdown) just shows its own
honest "nothing yet" state, since this script tracks none of that; only
Mark base log actually does something. Tagged `boat=MARKS` on the base's
own console/CSV so it's never confused with one of the virtual boats' own
sequential ids.

### Batching multiple fixes per send (TX_BATCH_SIZE)

`TX_BATCH_SIZE` (default **8**) packs that many consecutive fixes from one
boat into a single radio transmission instead of sending each on its own -
fewer, larger over-the-air transmissions instead of many small ones. Set
`TX_BATCH_SIZE=1` to go back to one frame per fix, this app's original
behavior (boatAgent.js never touches the batch frame type at all at that
setting). Whether batching is actually worth the added latency (fixes wait
to fill a batch, though never longer than `TX_INTERVAL_S` - see below)
depends on whether your bottleneck is per-transmission overhead or
per-byte airtime; see the XBee-PRO 900HP/XSC S3B's own `NP` command (max
RF payload - 256 bytes on the standard 900HP, but read-only and check it
yourself: the "900HP 200K" variant's higher RF data rate caps it much
lower, 100 bytes on this fleet's actual radios) for the ceiling a batch
frame stays comfortably under - the older batch frame (`MAX_BATCH_COUNT` in
protocol.js) is capped at 4 fixes (84 bytes) to fit that, and the delta-coded
frame described next carries 8 fixes in 83 bytes, which is why 8 is the default
(it was 4 before delta frames): this fleet's own congestion-testing (see
"Congestion-testing the radio" above) found batching comfortably improves
aggregate throughput at this hardware's real payload ceiling. A boat waits to
fill a batch only when no correction bursts are heard on its radio - in slot
mode it sends what it has gathered once per cycle instead (see "Sending in the
slot").

**Delta-coded frames (`TX_DELTA`, on by default).** Batches go out as *delta frames* (sync `0xE7`): the first
fix in full (19 bytes) and every later fix as its change from the one before (8 bytes), so a frame holds up to
**8 fixes in 83 bytes** (the older batch frame needed 84 bytes for 4). Sizes: 2 fixes 35 bytes, 4 fixes 51,
5 fixes 59, 8 fixes 83, against 46/84/111/168 as batch frames. Latitude and longitude are exact; fixes
after the first in a frame have their time rounded to 2 ms, speed to 0.5 knot (so within 0.25) and heading to 2
degrees (so within 1; the encoder works from what the decoder will rebuild, so nothing drifts along a frame).
A fix whose change does not fit - a GPS jump, a gap over 510 ms, a speed step over 63 knots - simply starts a
new frame (a turn of any size fits: heading changes go the short way round, up to 180 degrees), which always opens with a full fix, so frames are self-contained and a lost frame never corrupts the
next. A lone fix is the plain 26-byte frame. **Update the base before the boats**: the base decodes both
frame types, but a base that does not know `0xE7` ignores delta frames. `TX_DELTA=0` makes boats send the
older batch frame (4 fixes at most) for use with an old base; `TX_BATCH_SIZE` is then limited to 4 (up to 8 with
delta frames, the default).

Test it with the same tool "Congestion-testing the radio" above uses -
`radio-congestion` respects `TX_BATCH_SIZE` too, so you can compare real
transmission rates at different batch sizes (or against `TX_BATCH_SIZE=1`)
at your actual fleet size before ever touching a real boat:

```
BOAT_COUNT=30 TX_BATCH_SIZE=4 RADIO_PORT=/dev/cu.usbserial-A npm run radio-congestion
```

The console's own "X frames sent, Y tx/s actual average" line (and the
base's `[radio] link quality` log) reflect actual transmissions, not
fixes - with batching on, that number drops roughly in proportion to
`TX_BATCH_SIZE` for the same fix rate. No env var needs setting on a real
boat to get this - `TX_BATCH_SIZE=8` is already the default:

```
npm run boat
```

**Timestamps inside a batch.** A fix's time is always its own GPS
`timestamp` (the Redis sorted-set score), so a 10 Hz simulator produces fixes
100ms apart even when 8 arrive in one frame. The base stores no
arrival time in a fix: it used to stamp each unpacked fix with `new Date()`
(a `receivedAt`), which gave every fix in a batch the identical value. Track
points returned from Redis still carry a `receivedAt` field for existing
consumers, but it is now just the GPS timestamp, including for fixes stored
before this change.

### RTCM on the shared radio (telemetry and corrections on one radio)

If the radio on a boat's/base's serial port is also the RTK correction link (every radio on
the same network ID and `HP` - see `docs/xbee-radio-settings.md`), the RTK base's RTCM3
messages arrive on that same serial port, mixed in with position frames, marks and the rest.

- **Recognised, never an error.** `radioLink.js` (and the UDP simulator) now treat an RTCM3
  message as its own frame type: `0xD3`, a 10-bit length, the payload, and a CRC-24Q that must
  check out (`protocol.js`'s `decodeRtcm`). Before this, RTCM bytes looked like noise: the same
  5-second test stream produced 965 sync errors, because payload bytes that happen to equal one
  of our own sync bytes (`0xAA`, `0xBB`, ...) were taken for the start of a frame; now it
  produces none, and the telemetry frames in between all decode. A false `0xD3` with an
  implausible length (over 300 bytes) is rejected straight away, so it can't make the scanner
  wait on a frame that never arrives. A corrupted RTCM message costs a couple of sync errors and
  nothing around it.
- **Counted.** The rover counts what arrives over the radio (`radioRtcm` in `GET /api/stats`:
  frames, bytes, forwarded, last type). That is separate from `rtcm`, which counts what the GPS
  receiver reports applying (`UBX-RXM-RTCM`). `RTCM_LOG=1` prints one tight line
  per second per source instead of a line per message:
  ```
  [rtcm-radio] 449B 6msg MSM4 1005:stn 1074:GPS8 1084:GLO7 1094:GAL3 1124:BDS7 1230:bias
  [rtcm] 6/6 used: 1005 1074 1084 1094 1124 1230
  ```
  The first is what arrived over the radio (bytes, message count, MSM level, and the number
  of satellites in each constellation's message, each tagged with its RTCM message number (`1074:GPS8` = message 1074, GPS, 8 satellites); `->GPS` is added when `RTCM_FORWARD` also
  wrote them to the receiver, and `!set changed (...)` appears if a burst's set of messages
  differs from the previous one). The second is what the GPS receiver reports applying; it
  names any message not used, and any with a CRC failure. `RTCM_LOG=2` prints a decoded line
  per message instead, e.g. `[rtcm-radio] 1074 GPS 8sv 12c 129B` (`c` = signal cells) and
  `[rtcm] 1074 used`. `GPS_LOG_RTCM` is the old name for this setting. A base's telemetry station hears the same RTCM and simply ignores it.
- **A lost frame never strands a boat.** The base detects the start, a lap (the finish) and the fouls from two consecutive fixes it
  received that straddle a line - one fix on each side is all it needs - so the boat makes sure that pair is sent:
  - it watches its own full-rate (10 Hz) fixes for the same crossings (`eventBoost.js`); when it sees one it sends the two fixes just
    before it, which its gates had dropped, and every fix for the next 0.6 s, whatever state it is in (parked, no slot, backing off);
  - near a windward or leeward mark, or near the finish line heading upwind (`TX_SLOT_MARK_ZONE_M`, 80 m), it uses its whole slot, nothing is thinned
    away, and a boat under way is not paced (the mark roundings need several fixes inside the zone, so they rely on this);
  - a boat under way without a slot reports every 2 to 4 s, not every 15 s;
  - the distance gate counts a fix as reported only when its frame was actually written to the radio: if the scheduler drops it (queue
    full, too old, refused by the radio) the gate falls back to the last fix that really went out, so the next fix passes at once
    instead of a stationary boat staying silent until its 60 s heartbeat;
  - a parked boat whose report is not due yet keeps its newest fix for when it is, and repeats its first report once;
  - on the base, a fix that arrives late (older than one already seen) is not fed to the event detectors, so it cannot make a stale
    position the previous one and miss or double-count a crossing.
- **Warned about when missing.** A boat that does not hear the correction bursts is not slot-timed (it sends unslotted, on top
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
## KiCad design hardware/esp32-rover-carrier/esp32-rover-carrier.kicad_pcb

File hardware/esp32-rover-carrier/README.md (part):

# ESP32 rover carrier board (rev C)

A 134 × 53.34 mm, 2-layer motherboard for the ESP32 rover, laid out to fit the enclosure (the 2026-11-07 handoff).

Plugged into female sockets:
- **ArduSimple simpleRTK2B Budget (J1–J4):** XBee in its own socket, ZED UART2 off (`--role rover`), switch down.
- **Feather ESP32-S3 Reverse TFT (J5, J6):** on 8.5 mm stacking headers, display side up, USB-C at the front edge.

Soldered low on their own male headers, because there isn't height for sockets:
- **Adafruit LIS3DH (J8, J9)** and **Pololu S9V11F5 (J10):** under the ArduSimple, which leaves about 9.5 mm.
- **Adafruit bq24074 charger (J7), optional:** on 8.5 mm sockets its BATT and SYSOUT JSTs would hit the XBee's antenna plug.

The battery connects through a JST-PH socket on the back edge (J11), its plug facing the back wall.

The case for it is in [../esp32-rover-enclosure](../esp32-rover-enclosure), built from this board's `tools/layout.py`.

Everything is through-hole and hand-solderable. It replaces the loose wiring in
[docs/esp32-rover-wiring.pdf](../../docs/esp32-rover-wiring.pdf) and the harness in
[docs/esp32-rover-harness.pdf](../../docs/esp32-rover-harness.pdf).

From left to right: the ArduSimple (with the LIS3DH and the regulator under it), then the charger, then the Feather on
its own at the right end. The XBee's RP-SMA overhangs the ArduSimple's right edge, over the charger. Nothing sits above
the Feather's display, so the enclosure can have a window over it.

Rev C against rev B, for the enclosure:

- **12.5 mm shorter** (146.5 → 134 mm): the LIS3DH moved under the ArduSimple.
- **The regulator moved under the ArduSimple**, out of the charger's way.
- **The charger is soldered low and sits 3.22 mm back from the front edge**, so its DC jack stays inside the case's
  front wall. Only the two USB-C faces reach the front edge.
- **The battery JST moved to the back edge**, plug facing the back wall; JP1, TP1 and J12 moved behind the charger.
- **H3 sits between the charger and the Feather** with no screw: a post on the lid presses it down, so keep a 5 mm
  column above it clear. H1 and H2 screw to floor posts. H16 is gone: the case's fourth lid-screw boss sits in that
  front corner.

Rev B against rev A: the Feather moved to the far right, the bq24074 turned so its USB-C faces the front edge, and the
optional connections were added.

## Files

| File | What it is |
|---|---|
| `esp32-rover-carrier.kicad_pro` / `.kicad_sch` / `.kicad_pcb` | KiCad 10 project |
| `fab/esp32-rover-carrier-gerbers.zip` | Gerbers and drill files, ready to upload to JLCPCB |
| `fab/esp32-rover-carrier-schematic.pdf`, `fab/esp32-rover-carrier-board.pdf` | For review |
| `fab/bom.csv` | Parts list |
| `tools/layout.py` | Module positions and the netlist: the one place to change |
| `tools/gen_sch.py`, `tools/gen_pcb.py` | Regenerate the schematic and the routed board from `layout.py` |

To regenerate after a change to `layout.py`:

```bash
python3 tools/gen_sch.py && ~/Applications/KiCad/KiCad.app/Contents/Frameworks/Python.framework/Versions/Current/bin/python3 tools/gen_pcb.py
```

`gen_pcb.py` places the footprints, routes every net with its own grid router, adds GND stitching vias and pours ground on
both layers. Check the result with:

```bash
~/Applications/KiCad/KiCad.app/Contents/MacOS/kicad-cli pcb drc --schematic-parity esp32-rover-carrier.kicad_pcb
```

Rev C results: 0 violations, 0 unconnected items, 0 schematic-parity issues. The only warnings say that KiCad's library
tables aren't set up on this machine, and that the battery JST's outline meets the back edge (on purpose).

## Connections

| Net | Joins |
|---|---|
| GPS_TX | ArduSimple D0 (TX1) → Feather RX (GPIO 38) |
| GPS_RX | Feather TX (GPIO 39) → ArduSimple D1 (RX1) |
| XB_DOUT | ArduSimple D2 (XBEE TX / GPS RX2) → Feather D5 |
| XB_DIN | Feather D6 → ArduSimple D8 (XBEE RX / GPS TX2) |
| 3V3 | Feather 3V (both pins) → ArduSimple IOREF |
| 5V | S9V11F5 VOUT → ArduSimple 5V IN/OUT |
| VSYS | Feather BAT, S9V11F5 VIN, LIS3DH VIN, bq24074 OUT, JP1 pin 2 |
| BATT | Battery JST +, bq24074 VLIPO, JP1 pin 1 |
| SCL, SDA | Feather SCL/SDA ↔ LIS3DH SCL/SDA |
| ACC_INT | LIS3DH INT1 → Feather D10 |
| CHG_N, PGOOD_N | bq24074 ~CHG → Feather D11, ~PGOOD → Feather D12 (open drain; the firmware doesn't read them yet) |
| GND | Everything, plus both copper pours |

The firmware pins are unchanged (`feather_s3_reversetft_socket` build).

### Optional connections

These are wired but not used by the firmware yet, except `GPS_POWER_PIN`, which already exists as a build flag.
[OPTIONAL-CONNECTIONS.md](OPTIONAL-CONNECTIONS.md) explains what each one gives and what it would take to use it.

| Net | Joins | Use |
|---|---|---|
| GPS_EN | Feather A0 (GPIO 18) → pad TP2 | Wire TP2 to the S9V11F5's EN pad, then build with `-DGPS_POWER_PIN=18`. Deep sleep then cuts the ArduSimple and the XBee (about 20–50 mA saved overnight). The GPS loses its almanac unless V_BCKP is supplied, so expect slower fixes after a sleep. |
| GPS_PPS | ArduSimple D13 (TIMEPULSE) → Feather A1 (GPIO 17) | The ZED's 1 PPS edge, for exact timing |
| GPS_EXTINT | Feather A2 (GPIO 16) → ArduSimple D12 (EXTINT) | A hardware wake or time mark for the ZED |
| CHG_DIS | Feather A3 (GPIO 15) → bq24074 ~CE | High stops charging. The bq's 10 kΩ pull-down keeps charging on while the pin floats. |
| ACC_INT2 | LIS3DH INT2 → Feather A4 (GPIO 14) | A second accelerometer interrupt. It's an RTC GPIO, so it can wake the board. |
| FEATHER_EN | Feather EN → J12 pin 1 (pin 2 GND) | Short J12 to switch the Feather off. The regulator and ArduSimple stay on battery power. For a true off switch without a charger, put the switch on JP1 instead of the shunt. |

Feather D9, D13, A5, SCK, MOSI and MISO are still free. The ZED's I2C isn't wired.

There are two differences from the hand wiring:

- **The LIS3DH runs from VSYS, not the Feather's 3V.** The breakout has its own 3.3 V regulator. This shortens the wiring,
  and VSYS stays on in deep sleep, so motion wake still works.
- **The S9V11F5 has no EN pin.** It has only VIN, GND and VOUT; its enable is a small solder pad on the module (Pololu's drawing shows only the three holes). That's why
  GPS_EN goes to a wire pad (TP2) rather than to the socket.

## Battery and charger: JP1

- **No bq24074 fitted:** put the shunt on JP1. The battery feeds VSYS directly, as it does now.
- **bq24074 fitted:** remove the shunt. The battery feeds the charger, and the charger's OUT feeds VSYS. Charge it through
  the bq24074's USB-C on the front edge.

Never fit both. With both in place, the shunt bypasses the charger's battery control. JP1 sits behind the charger, on
the back edge beside the battery JST. The charger's own BATT and SYSOUT JSTs stay empty: the battery and VSYS go
through its 11-pin header (VLIPO pin 2, OUT pin 4).

## Check before ordering

1. **Print the board at 100 % and press the modules' pins into the paper.**
   - Print `fab/esp32-rover-carrier-fitcheck.pdf` at 100 % ("Actual size"). It shows the outlines, pads and real drill
     holes with no copper pour. The board outline should measure 134 × 53.34 mm.
   - The ArduSimple's header pattern is the Arduino Uno R3 layout. I measured it against ArduSimple's pinout image, not a
     drawing.
   - The Feather, LIS3DH and bq24074 positions come from Adafruit's own board files.
2. **Check the S9V11F5 pin order on your module.** The board expects VIN, GND (square pad), VOUT. VOUT is the pin the
   "VOUT→" arrow on the module points to.
3. **Check that your LIS3DH matches the 2809 pinout:**
   - The VIN, 3Vo, GND, SCL, SDA, INT1 row is 0.5" from the CS, SDO, ADC1–3, INT2 row.
   - The board is 0.7 × 1.0".
4. **Check clearance under the ArduSimple.** The case expects about 9.5 mm between the carrier and the ArduSimple's
   underside. Under it are the LIS3DH and the S9V11F5, each soldered on a 2.5 mm header (about 5 mm tall in all), plus
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
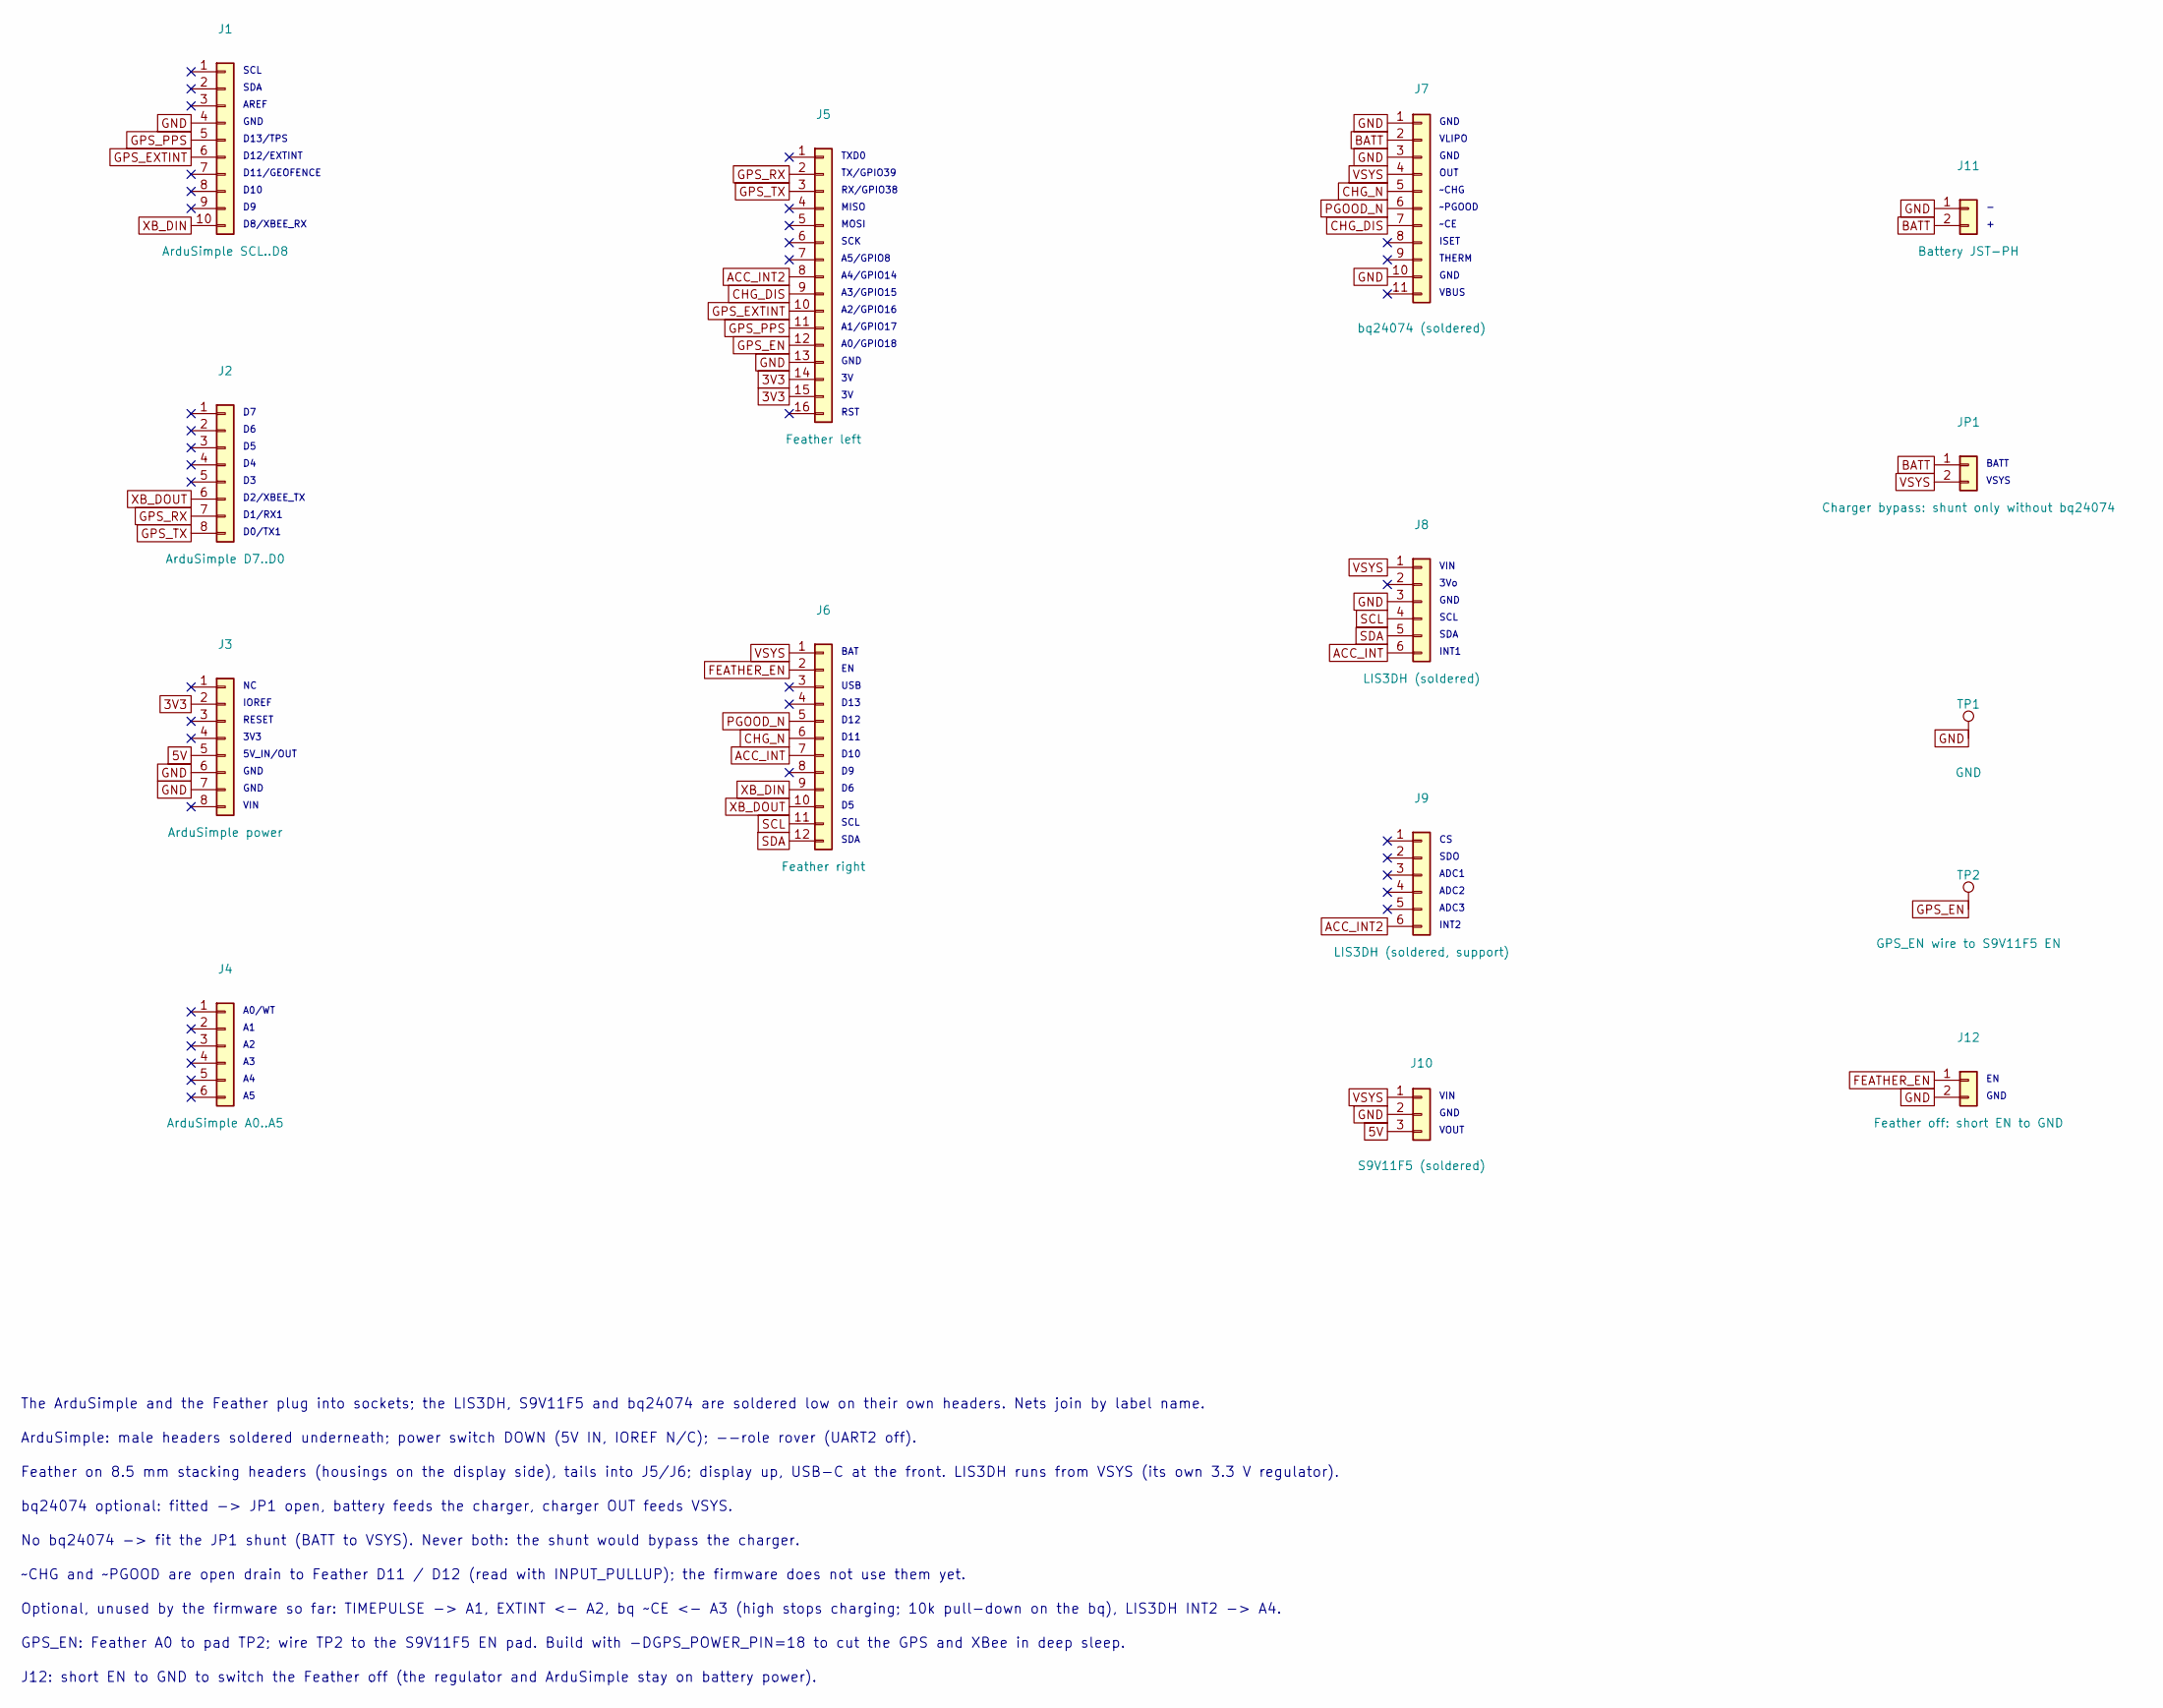
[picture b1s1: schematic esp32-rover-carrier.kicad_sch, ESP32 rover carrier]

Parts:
J1: ArduSimple SCL..D8; PinSocket_1x10_P2.54mm_Vertical
J2: ArduSimple D7..D0; PinSocket_1x08_P2.54mm_Vertical
J3: ArduSimple power; PinSocket_1x08_P2.54mm_Vertical
J4: ArduSimple A0..A5; PinSocket_1x06_P2.54mm_Vertical
J5: Feather left; PinSocket_1x16_P2.54mm_Vertical
J6: Feather right; PinSocket_1x12_P2.54mm_Vertical
J7: bq24074 (soldered); PinHeader_1x11_P2.54mm_Vertical
J8: LIS3DH (soldered); PinHeader_1x06_P2.54mm_Vertical
J9: LIS3DH (soldered, support); PinHeader_1x06_P2.54mm_Vertical
J10: S9V11F5 (soldered); PinHeader_1x03_P2.54mm_Vertical
J11: Battery JST-PH; JST_PH_S2B-PH-K_1x02_P2.00mm_Horizontal
J12: Feather off: short EN to GND; PinHeader_1x02_P2.54mm_Vertical
JP1: Charger bypass: shunt only without bq24074; PinHeader_1x02_P2.54mm_Vertical
TP1: GND; TestPoint_Pad_D1.5mm
TP2: GPS_EN wire to S9V11F5 EN; TestPoint_THTPad_D2.0mm_Drill1.0mm

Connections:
3V3: J3.2, J5.14, J5.15
5V: J3.5, J10.3
ACC_INT: J6.7, J8.6
ACC_INT2: J5.8, J9.6
BATT: J7.2, J11.2, JP1.1
CHG_DIS: J5.9, J7.7
CHG_N: J6.6, J7.5
FEATHER_EN: J6.2, J12.1
GND: J1.4, J3.6, J3.7, J5.13, J7.1, J7.3, J7.10, J8.3, J10.2, J11.1, J12.2, TP1.1
GPS_EN: J5.12, TP2.1
GPS_EXTINT: J1.6, J5.10
GPS_PPS: J1.5, J5.11
GPS_RX: J2.7, J5.2
GPS_TX: J2.8, J5.3
PGOOD_N: J6.5, J7.6
SCL: J6.11, J8.4
SDA: J6.12, J8.5
VSYS: J6.1, J7.4, J8.1, J10.1, JP1.2
XB_DIN: J1.10, J6.9
XB_DOUT: J2.6, J6.10

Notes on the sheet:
SCL
SDA
AREF
GND
D13/TPS
D12/EXTINT
D11/GEOFENCE
D10
D8/XBEE_RX
D2/XBEE_TX
D1/RX1
D0/TX1
IOREF
RESET
3V3
5V_IN/OUT
VIN
A0/WT
VLIPO
OUT
~CHG
~PGOOD
~CE
ISET
THERM
VBUS
3Vo
INT1
SDO
ADC1
ADC2
ADC3
INT2
VOUT
TXD0
TX/GPIO39
RX/GPIO38
MISO
MOSI
SCK

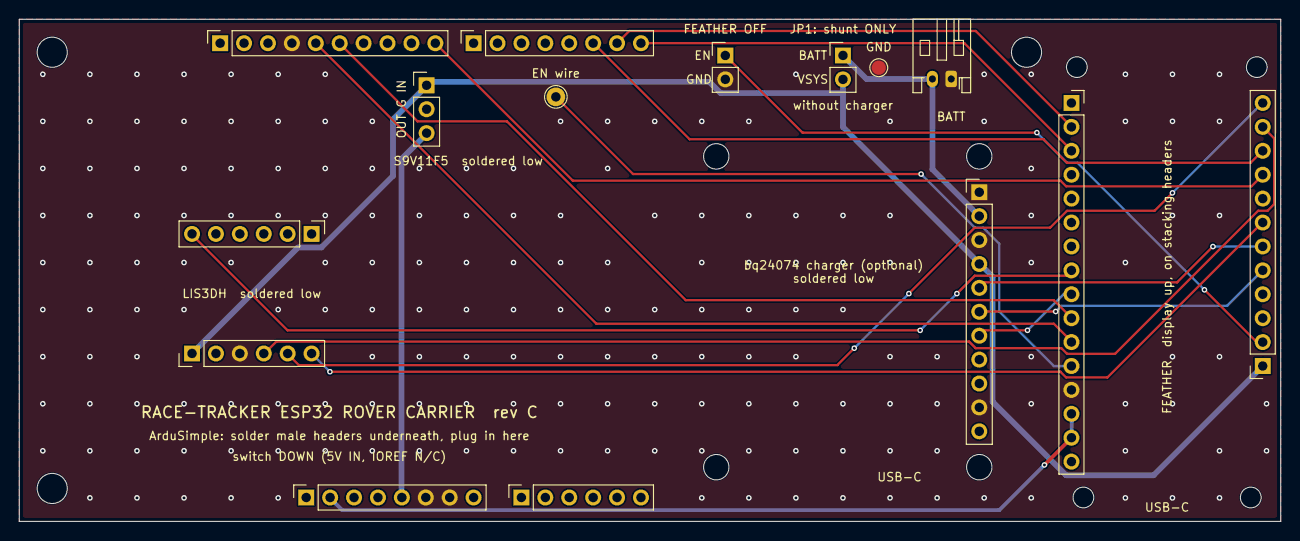
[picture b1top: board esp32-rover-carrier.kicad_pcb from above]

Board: 2 copper layers, 134.0 x 53.3 mm, 26 parts (0 on the bottom side), 20 nets.

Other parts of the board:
H1, H2, H3: MountingHole_3.2mm_M3
H4, H5, H6, H7: MountingHole_2.7mm_M2.5
H12, H13, H14, H15: MountingHole_2.2mm_M2
